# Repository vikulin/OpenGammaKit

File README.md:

# OpenGammaKit

## PCB front and back side

<table>
  <tr>
    <td align="center">
      
      <br><b>Front view</b>
    </td>
    <td align="center">
      
      <br><b>Back view</b>
    </td>
  </tr>
</table>

**OpenGammaKit** is an open-source gamma spectrometer hardware platform, inspired by the excellent [Open-Gamma-Detector](https://github.com/OpenGammaProject/Open-Gamma-Detector). It takes the original schematic and redesigns the PCB using **KiCad** (originally designed in EasyEDA), making the project more accessible and modifiable for open hardware enthusiasts.

OpenGammaKit is designed to be affordable, reliable, and easy to integrate with embedded systems, mobile devices, or PCs—ideal for DIY nuclear instrumentation, educational labs, or citizen science.

---

## Order the PCB or PCB + Assembly

You can order the **Open Gamma Kit** PCB or a fully assembled board from PCBWay or any other PCB manufacturer.
Also Epic Crystal 1inch NaI(Tl) crystal can be used for the prototype:
[NaI(Tl) crystal](https://www.epic-scintillator.com/NaI-scintillator-1inchx1inch)

---

## 🔧 Features

- ✅ Based on the **Open-Gamma-Detector** schematic  
- ✅ Complete redesign in **KiCad** with improved layout and routing  
- ✅ USB serial communication (compatible with Android 7.0+ and PCs)  
- ✅ Compatible with [OGK Inspector](https://github.com/vikulin/OGK-Inspector) Android app and [OGK Firmware](https://github.com/vikulin/OGK-Firmware) 
- ✅ Real-time gamma spectrum output and spectrometer integration  
- ✅ Works with scintillation detectors (e.g., CsI(Tl), NaI(Tl), etc.)  
- ✅ Open and editable source files for schematics and PCB

---

## 📘Assembly guide, 3D models for enclosure

https://github.com/vikulin/OGK-3D-Models

---

## 📂 Repository Contents

- `/docs/` – Spectrum([OGK Inspector](https://github.com/vikulin/OGK-Inspector))
- `/kicad-libraries/` – KiCad libraries, including custom footprints

---

## 📷 3D render previews of the boards

<p align="center">
  <br>
  
  <br>
  
</p>

---

## 📦 Release Contents

OpenGammaKit releases version **0.1.5.5** and later include all the fabrication files required to manufacture and assemble the OpenGammaKit gamma spectrometer hardware:

| File Name                                     | Description                                                                |
| --------------------------------------------- | -------------------------------------------------------------------------- |
| `open-gamma-kit-gerber-files-<version>.zip`   | 🟢 Complete Gerber and Drill files for PCB fabrication.                    |
| `open-gamma-kit-centroid-file-<version>.csv`  | 📍 Centroid (Pick-and-Place) file in mils for automated assembly.          |
| `open-gamma-kit-<version>.pdf`                | 📄 PDF documentation                                                       |
| `BOM.csv`                                     | 📋 Bill of Materials (not archived — listed separately).                   |

📁 **Location**: All files are available in the [Assets](https://github.com/vikulin/OpenGammaKit/releases) release section.

---

## 🧠 Companion Projects

- **OGK Inspector (Android App)**  
  View spectra, calculate resolution, access terminal mode  
  👉 [OGK-Inspector on GitHub](https://github.com/vikulin/OGK-Inspector)

- **OGK Firmware**  
  USB serial interface firmware for supported microcontrollers  
  👉 [OGK Firmware Repository](https://github.com/vikulin/OGK-Firmware)

---

## Spectrum of ²⁴¹Am source measured with NaI(Tl) detector
| Element | Symbol | Atomic Number | Mass Number |
|---------|--------|----------------|--------------|
| Americium | Am     | 95             | 241          |

The spectrum clearly shows two gamma peaks at **59.54 keV** and **26.35 keV**, both corresponding to emissions from ²⁴¹Am:

- The **59.54 keV** peak is the most intense and commonly used for energy calibration.
- The **26.35 keV** peak is weaker but still visible, depending on detector resolution and shielding conditions.

<p align="center">
  <br>
  
</p>

> 📌 These lines are useful for calibration and spectral identification in low-energy gamma spectroscopy using NaI(Tl) detectors.

---

## 📜 License

This project is licensed under the **GNU General Public License v3.0**.  
See the [LICENSE](LICENSE) file for details.

---

## 🙌 Acknowledgements

- Based on the original design by [OpenGammaProject](https://github.com/OpenGammaProject/Open-Gamma-Detector)  
- Thanks to the open hardware and spectroscopy communities!

---

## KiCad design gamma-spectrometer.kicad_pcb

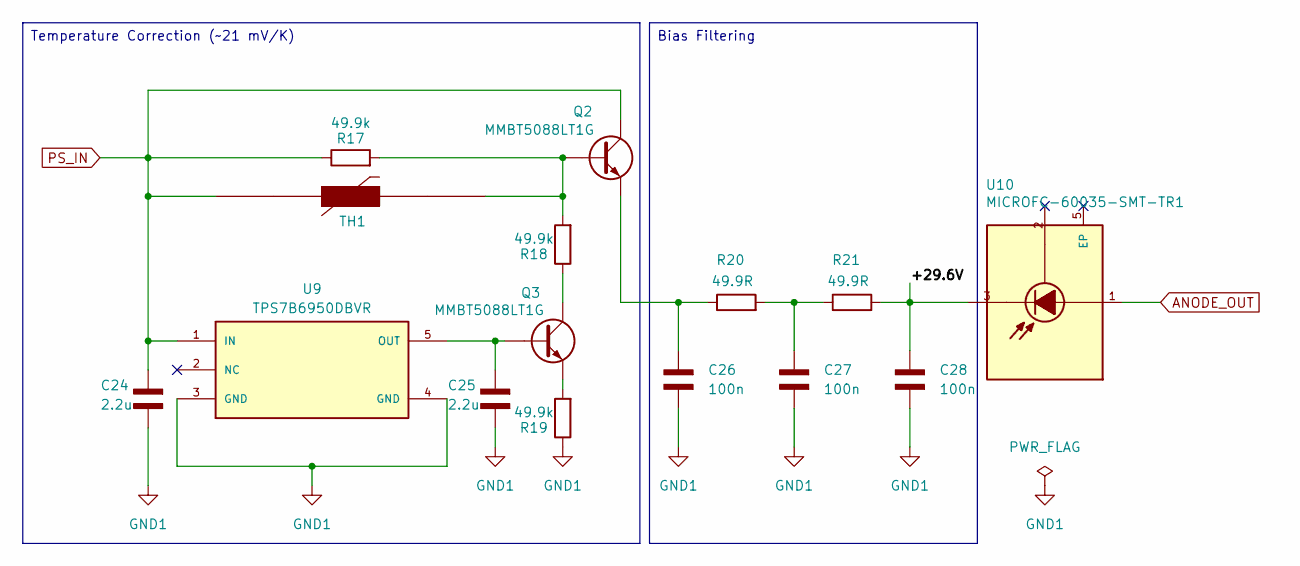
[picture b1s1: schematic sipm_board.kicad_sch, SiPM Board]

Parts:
C24, C25: 2.2u; C_0603_1608Metric
C26, C27, C28: 100n; CAPC1608X90N; PARTREV NA
Q2, Q3: MMBT5088LT1G; SOT95P237X111-3N
R17, R18, R19: 49.9k; RES_ERJ3EKF4992V
R20, R21: 49.9R; RES_ERJ3EKF49R9V
TH1: Thermistor_PTC; NTCS0603E3103FLT
U9: TPS7B6950DBVR; SOT95P280X145-5N
U10: MICROFC-60035-SMT-TR1; XDCR_MICROFC-60035-SMT-TR1; PARTREV 31 JUL 2018

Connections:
/SiPM Board/+29.6V: C28.2, R21.2, U10.3
ANODE_OUT: U10.1
GND1: C24.2, C25.2, C26.1, C27.1, C28.1, R19.1, U9.3 (GND), U9.4 (GND)
unnamed: C27.2, R20.2, R21.1
unnamed: Q2.2 (B), R17.2, R18.2, TH1.1
unnamed: C26.2, Q2.3 (E), R20.1
unnamed: C25.1, Q3.2 (B), U9.5 (OUT)
unnamed: Q3.1 (C), R18.1
unnamed: Q3.3 (E), R19.2
PS_IN: C24.1, Q2.1 (C), R17.1, TH1.2, U9.1 (IN)

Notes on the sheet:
Bias Filtering
Temperature Correction (~21 mV/K)

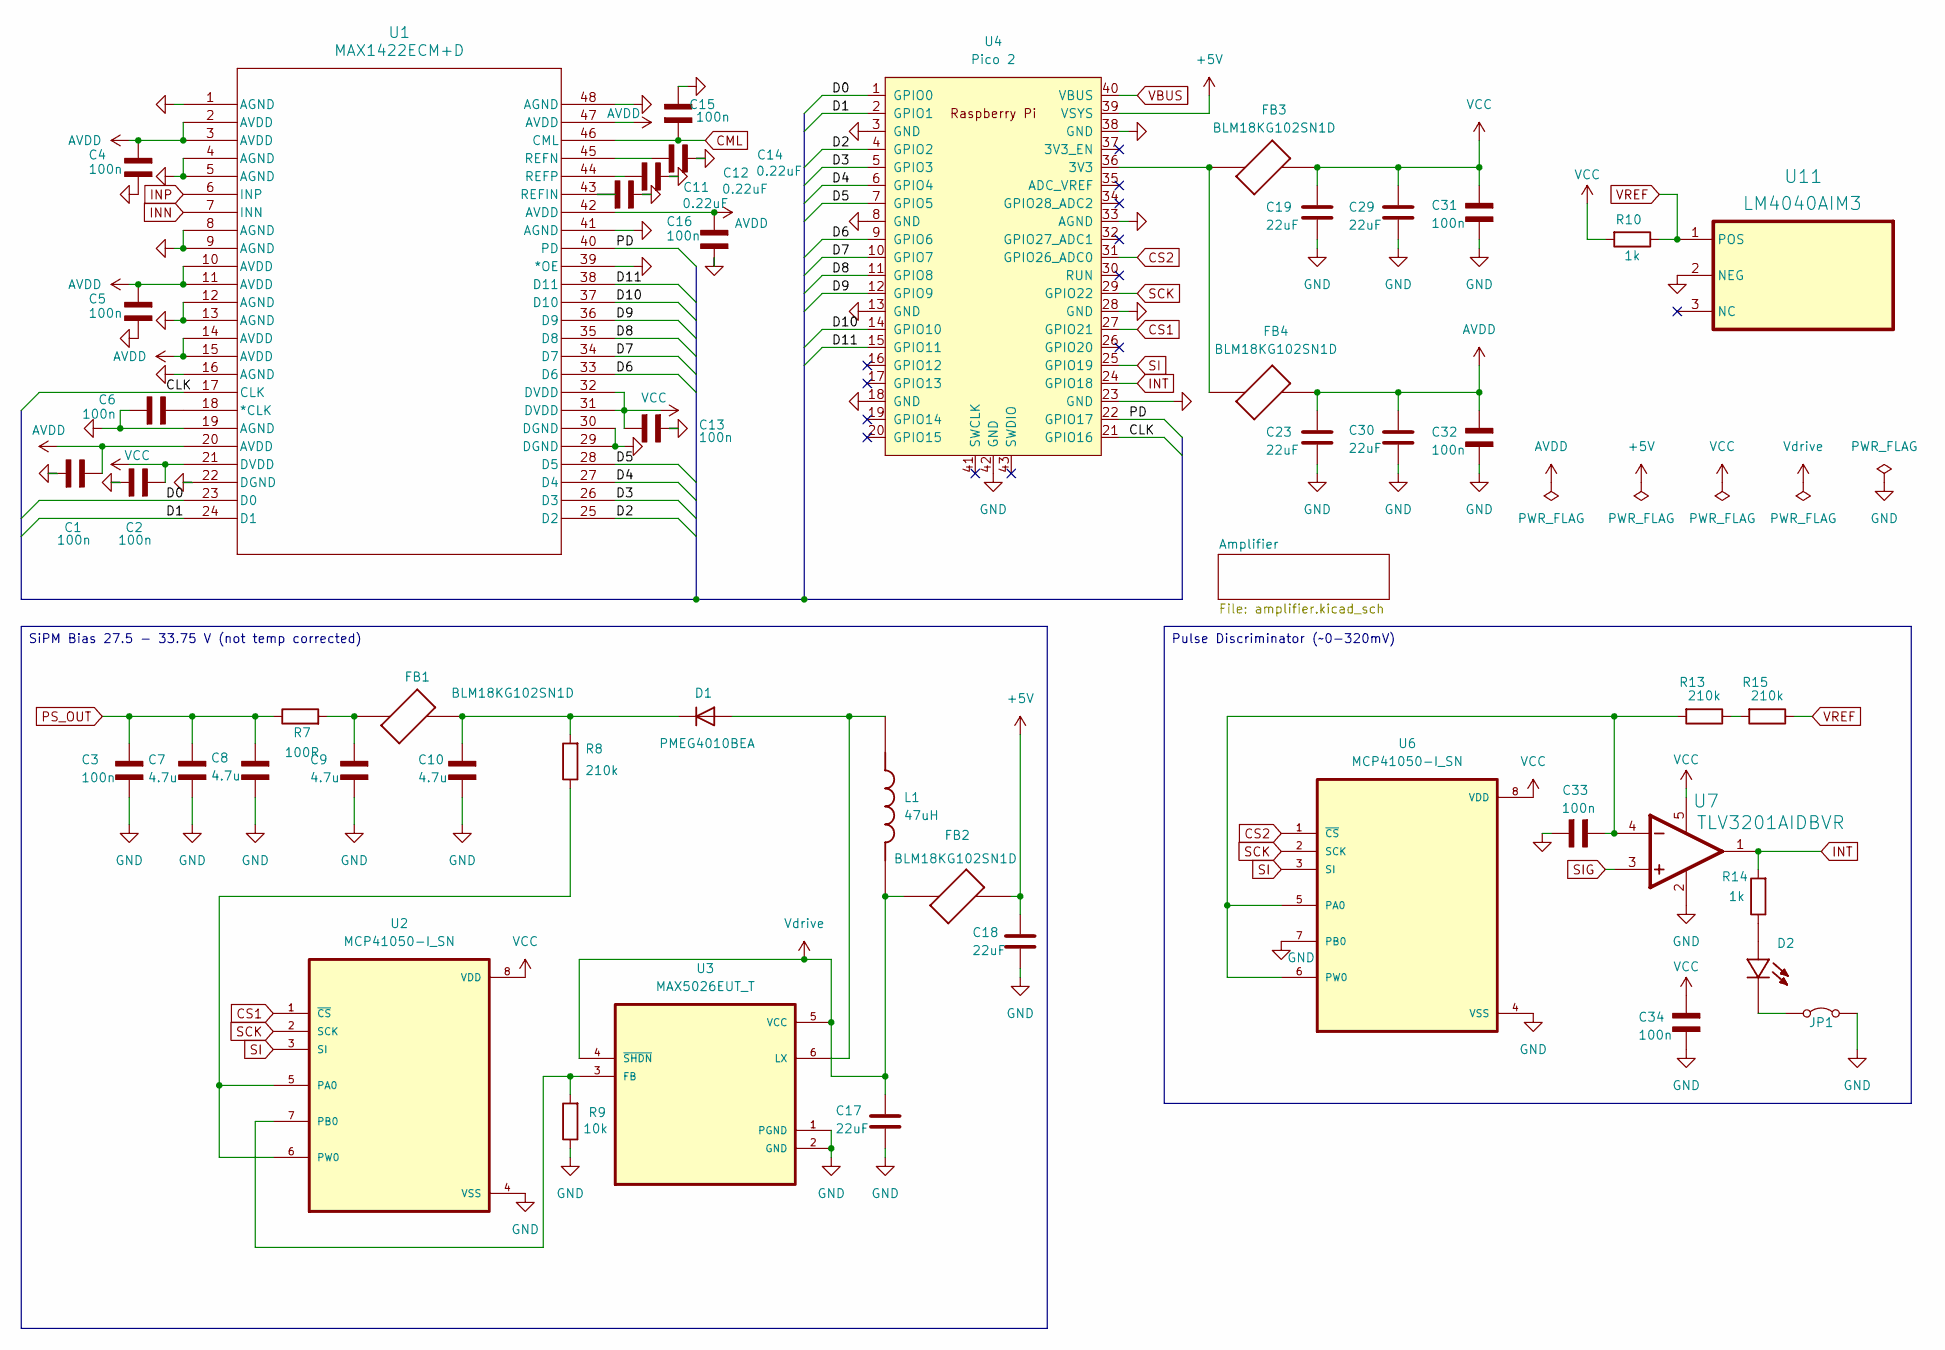
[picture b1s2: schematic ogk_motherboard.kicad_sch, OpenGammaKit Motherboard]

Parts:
C1, C2, C3, C4, C5, C6, C13, C15, C16, C31, C32, C33, C34: 100n; CAPC1608X90N; PARTREV NA
C7, C8, C9, C10: 4.7u; CAPC2012X140N
C11, C12, C14: 0.22uF; CAPC1608X90N
C17, C18, C19, C23, C29, C30: 22uF; CAPC1608X90N
D1: PMEG4010BEA; DIO_BZX384-C30_115
D2: LTST-C190KGKT; LEDC1608X35N
FB1, FB2, FB3, FB4: BLM18KG102SN1D; BEADC1608X95N
JP1: SolderJumper-2_P1.3mm_Open_TrianglePad1.0x1.5mm
L1: 47uH; IND_NRS4018T470MDGJ; PARTREV 2021.10.25
R7: 100R; RES_ERJ3EKF1000V
R8, R13, R15: 210k; RES_ERJ3EKF2103V
R9: 10k; RES_ERJ3EKF1002V
R10, R14: 1k; RES_ERJ3EKF1001V
U1: MAX1422ECM+D; 21-0054G_48_MXM
U2, U6: MCP41050-I_SN; SOIC127P600X175-8N
U3: MAX5026EUT_T; SOT95P280X145-6N
U4: Pico 2; RPi_Pico_SMD_TH
U7: TLV3201AIDBVR; SOT95P280X145-5N
U11: LM4040AIM3; SOT95P237X112-3N

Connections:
+5V: C18.1, FB2.2, U4.39 (VSYS)
/Motherboard/CLK: U1.17 (CLK), U4.21 (GPIO16)
/Motherboard/D0: U1.23 (D0), U4.1 (GPIO0)
/Motherboard/D1: U1.24 (D1), U4.2 (GPIO1)
/Motherboard/D2: U1.25 (D2), U4.4 (GPIO2)
/Motherboard/D3: U1.26 (D3), U4.5 (GPIO3)
/Motherboard/D4: U1.27 (D4), U4.6 (GPIO4)
/Motherboard/D5: U1.28 (D5), U4.7 (GPIO5)
/Motherboard/D6: U1.33 (D6), U4.9 (GPIO6)
/Motherboard/D7: U1.34 (D7), U4.10 (GPIO7)
/Motherboard/D8: U1.35 (D8), U4.11 (GPIO8)
/Motherboard/D9: U1.36 (D9), U4.12 (GPIO9)
/Motherboard/D10: U1.37 (D10), U4.14 (GPIO10)
/Motherboard/D11: U1.38 (D11), U4.15 (GPIO11)
/Motherboard/PD: U1.40 (PD), U4.22 (GPIO17)
AVDD: C1.2, C4.2, C5.2, C16.2, C23.1, C30.1, C32.2, FB4.2, U1.2 (AVDD), U1.3 (AVDD), U1.10 (AVDD), U1.11 (AVDD), U1.14 (AVDD), U1.15 (AVDD), U1.20 (AVDD), U1.42 (AVDD), U1.47 (AVDD)
CML: C15.2, U1.46 (CML); also elsewhere on the board
CS1: U2.1 (~CS), U4.27 (GPIO21)
CS2: U4.31 (GPIO26_ADC0), U6.1 (~CS)
GND: C1.1, C2.1, C3.1, C4.1, C5.1, C6.1, C7.2, C8.2, C9.2, C10.2, C11.2, C12.2, C13.1, C14.2, C15.1, C16.1, C17.2, C18.2, C19.2, C23.2, C29.2, C30.2, C31.1, C32.1, C33.2, C34.1, JP1.2 (B), R9.1, U1.1 (AGND), U1.4 (AGND), U1.5 (AGND), U1.8 (AGND), U1.9 (AGND), U1.12 (AGND), U1.13 (AGND), U1.16 (AGND), U1.19 (AGND), U1.22 (DGND), U1.29 (DGND), U1.30 (DGND), U1.39 (*OE), U1.41 (AGND), U1.48 (AGND), U2.4 (VSS), U3.1 (PGND), U3.2 (GND), U4.3 (GND), U4.8 (GND), U4.13 (GND), U4.18 (GND), U4.23 (GND), U4.28 (GND), U4.33 (AGND), U4.38 (GND), U4.42 (GND), U6.4 (VSS), U6.7 (PB0), U7.2 (GND), U11.2 (NEG); also elsewhere on the board
INN: U1.7 (INN); also elsewhere on the board
INP: U1.6 (INP); also elsewhere on the board
INT: R14.2, U4.24 (GPIO18), U7.1 (OUT)
unnamed: C9.1, FB1.1, R7.2
unnamed: D1.2 (A), L1.1, U3.6 (LX)
unnamed: C10.1, D1.1 (K), FB1.2, R8.2
unnamed: D2.A, R14.1
unnamed: D2.C, JP1.1 (A)
unnamed: R13.1, R15.2
unnamed: C6.2, U1.18 (*CLK)
unnamed: C11.1, U1.43 (REFIN)
unnamed: C14.1, U1.45 (REFN)
unnamed: C12.1, U1.44 (REFP)
unnamed: R8.1, U2.5 (PA0), U2.6 (PW0)
unnamed: R9.2, U2.7 (PB0), U3.3 (FB)
unnamed: FB3.1, FB4.1, U4.36 (3V3)
unnamed: C33.1, R13.2, U6.5 (PA0), U6.6 (PW0), U7.4 (IN-)
PS_OUT: C3.2, C7.1, C8.1, R7.1
SCK: U2.2 (SCK), U4.29 (GPIO22), U6.2 (SCK)
SI: U2.3 (SI), U4.25 (GPIO19), U6.3 (SI)
SIG: U7.3 (IN+); also elsewhere on the board
VBUS: U4.40 (VBUS)
VCC: C2.2, C13.2, C19.1, C29.1, C31.2, C34.2, FB3.2, R10.2, U1.21 (DVDD), U1.31 (DVDD), U1.32 (DVDD), U2.8 (VDD), U6.8 (VDD), U7.5 (VCC); also elsewhere on the board
VREF: R10.1, R15.1, U11.1 (POS)
Vdrive: C17.1, FB2.1, L1.2, U3.4 (~SHDN), U3.5 (VCC)

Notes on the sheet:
Pulse Discriminator (~0-320mV)
SiPM Bias 27.5 - 33.75 V (not temp corrected)

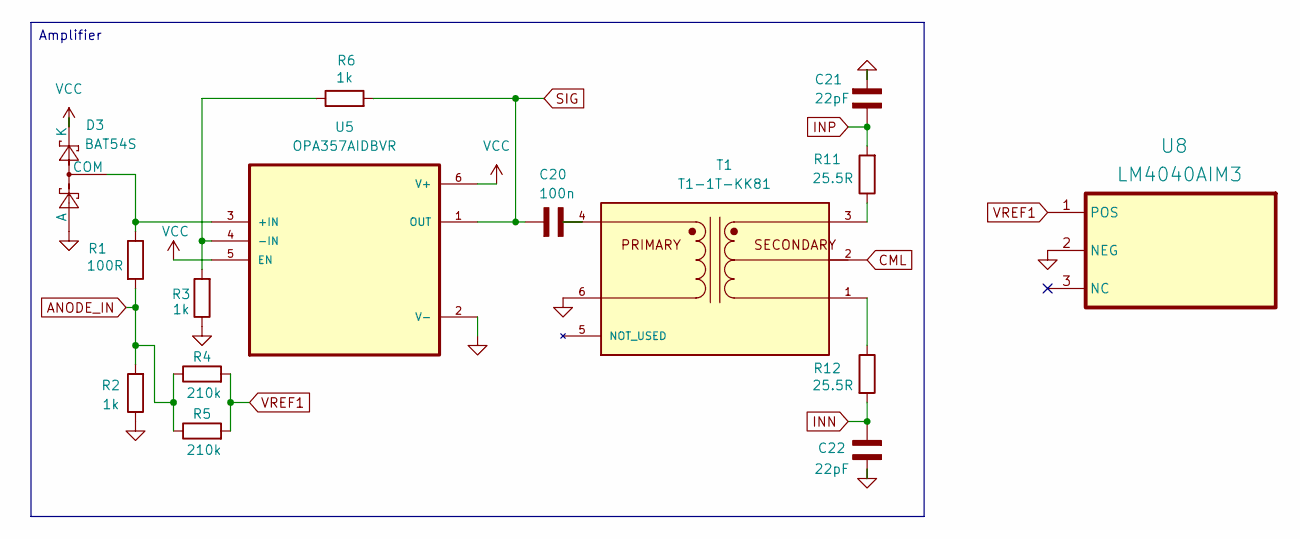
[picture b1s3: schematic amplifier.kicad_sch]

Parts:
C20: 100n; CAPC1608X90N; PARTREV NA
C21, C22: 22pF; CAPC1608X90N; PARTREV 11-Oct-17
D3: BAT54S; SOT-23
R1: 100R; RES_ERJ3EKF1000V
R2, R3, R6: 1k; RES_ERJ3EKF1001V
R4, R5: 210k; RES_ERJ3EKF2103V; PARTREV 3/1/2020
R11, R12: 25.5R; RES_ERJ3EKF25R5V
T1: T1-1T-KK81; XFMR_T1-1T-KK81_; PARTREV B
U5: OPA357AIDBVR; SOT95P280X145-6N
U8: LM4040AIM3; SOT95P237X112-3N

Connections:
ANODE_IN: R1.2, R2.2, R4.1, R5.1
CML: T1.2; also elsewhere on the board
GND: C21.1, C22.1, D3.1 (A), R2.1, R3.1, T1.6, U5.2 (V-), U8.2 (NEG); also elsewhere on the board
INN: C22.2, R12.2; also elsewhere on the board
INP: C21.2, R11.2; also elsewhere on the board
unnamed: C20.2, T1.4
unnamed: D3.3 (COM), R1.1, U5.3 (+IN)
unnamed: R11.1, T1.3
unnamed: R12.1, T1.1
unnamed: R3.2, R6.1, U5.4 (-IN)
SIG: C20.1, R6.2, U5.1 (OUT); also elsewhere on the board
VCC: D3.2 (K), U5.5 (EN), U5.6 (V+); also elsewhere on the board
VREF1: R4.2, R5.2, U8.1 (POS)

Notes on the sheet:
Amplifier

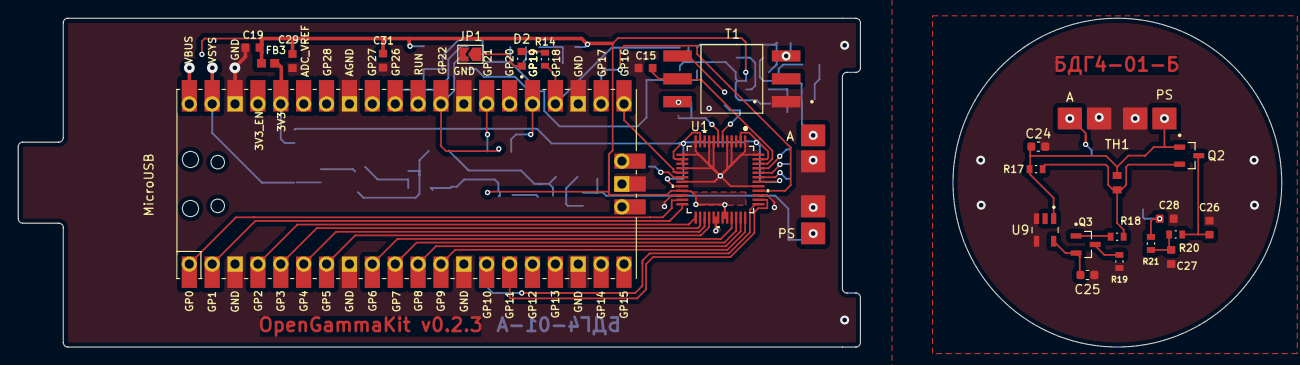
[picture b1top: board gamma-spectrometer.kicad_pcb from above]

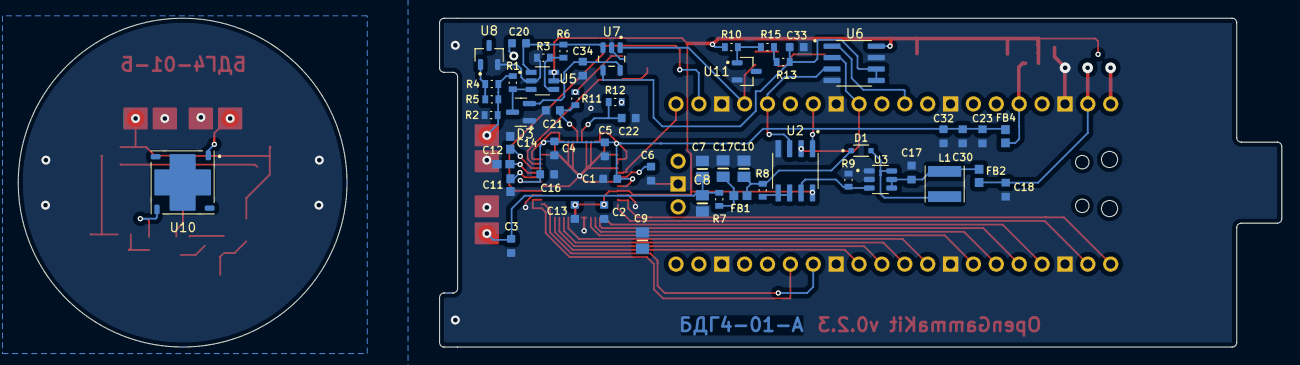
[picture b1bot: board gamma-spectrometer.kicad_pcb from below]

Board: 2 copper layers, 140.3 x 36.5 mm, 79 parts (54 on the bottom side), 60 nets.

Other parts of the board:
C17#2: 4.7u; CAPC2012X140N

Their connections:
GND: C17#2.2; also elsewhere on the board

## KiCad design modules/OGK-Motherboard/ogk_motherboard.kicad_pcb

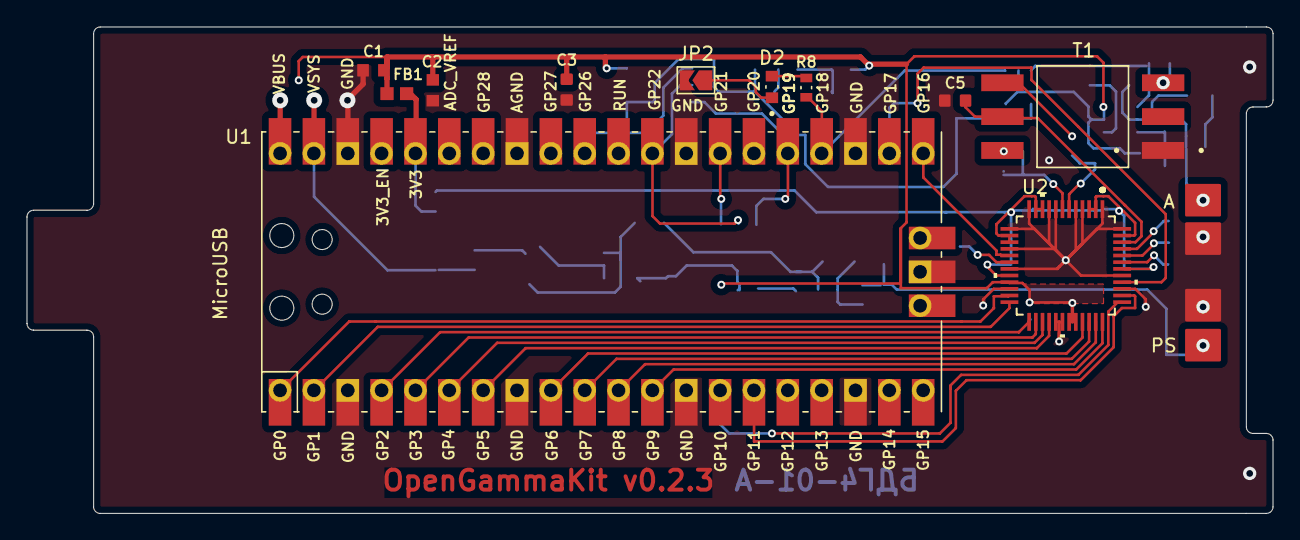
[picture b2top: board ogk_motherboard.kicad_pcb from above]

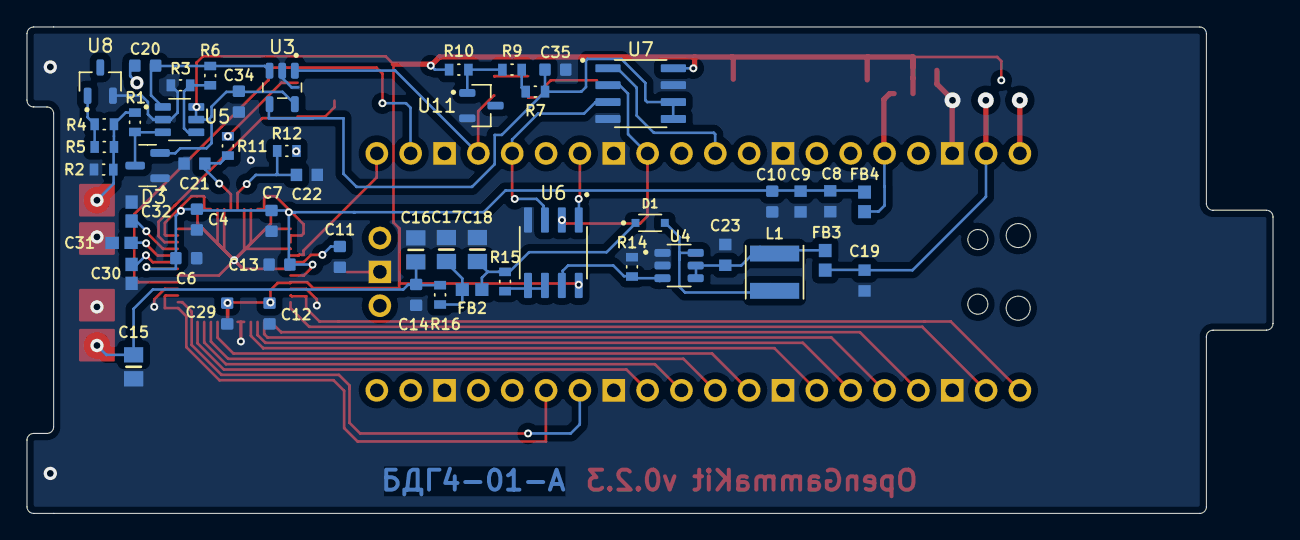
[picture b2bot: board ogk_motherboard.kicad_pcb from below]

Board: 2 copper layers, 93.5 x 36.5 mm, 63 parts (52 on the bottom side), 51 nets.

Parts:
C1, C2, C8, C9, C19, C23: 22uF; CAPC1608X90N
C3, C4, C5, C6, C7, C10, C11, C12, C13, C14, C20, C29, C34, C35: 100n; CAPC1608X90N
C15, C16, C17, C18: 4.7u; CAPC2012X140N
C21, C22: 22pF; CAPC1608X90N
C30, C31, C32: 0.22uF; CAPC1608X90N
D1: PMEG4010BEA; DIO_BZX384-C30_115
D2: LTST-C190KGKT; LEDC1608X35N
D3: BAT54S; SOT-23
FB1, FB2, FB3, FB4: BLM18KG102SN1D; BEADC1608X95N
JP2: SolderJumper-2_P1.3mm_Open_TrianglePad1.0x1.5mm
L1: 47uH; IND_NRS4018T470MDGJ
R1, R16: 100R; RES_ERJ3EKF1000V
R2, R3, R6, R8, R10: 1k; RES_ERJ3EKF1001V
R4, R5, R7, R9, R15: 210k; RES_ERJ3EKF2103V
R11, R12: 25.5R; RES_ERJ3EKF25R5V
R14: 10k; RES_ERJ3EKF1002V
T1: T1-1T-KK81; XFMR_T1-1T-KK81_
U1: Pico 2; RPi_Pico_SMD_TH
U2: MAX1422ECM+D; 21-0054G_48_MXM
U3: TLV3201AIDBVR; SOT95P280X145-5N
U4: MAX5026EUT_T; SOT95P280X145-6N
U5: OPA357AIDBVR; SOT95P280X145-6N
U6, U7: MCP41050-I_SN; SOIC127P600X175-8N
U8, U11: LM4040AIM3; SOT95P237X112-3N

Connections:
+5V: C19.1, FB3.2, U1.39 (VSYS)
/CLK: U1.21 (GPIO16), U2.17 (CLK)
/D0: U1.1 (GPIO0), U2.23 (D0)
/D1: U1.2 (GPIO1), U2.24 (D1)
/D2: U1.4 (GPIO2), U2.25 (D2)
/D3: U1.5 (GPIO3), U2.26 (D3)
/D4: U1.6 (GPIO4), U2.27 (D4)
/D5: U1.7 (GPIO5), U2.28 (D5)
/D6: U1.9 (GPIO6), U2.33 (D6)
/D7: U1.10 (GPIO7), U2.34 (D7)
/D8: U1.11 (GPIO8), U2.35 (D8)
/D9: U1.12 (GPIO9), U2.36 (D9)
/D10: U1.14 (GPIO10), U2.37 (D10)
/D11: U1.15 (GPIO11), U2.38 (D11)
/PD: U1.22 (GPIO17), U2.40 (PD)
ANODE_IN: R1.2, R2.2, R4.1, R5.1
AVDD: C4.2, C6.2, C7.2, C8.1, C9.1, C10.2, C13.2, FB4.2, U2.2 (AVDD), U2.3 (AVDD), U2.10 (AVDD), U2.11 (AVDD), U2.14 (AVDD), U2.15 (AVDD), U2.20 (AVDD), U2.42 (AVDD), U2.47 (AVDD)
CML: C5.2, T1.2, U2.46 (CML)
CS1: U1.27 (GPIO21), U6.1 (~CS)
CS2: U1.31 (GPIO26_ADC0), U7.1 (~CS)
GND: C1.2, C2.2, C3.1, C4.1, C5.1, C6.1, C7.1, C8.2, C9.2, C10.1, C11.1, C12.1, C13.1, C14.1, C15.2, C16.2, C17.2, C18.2, C19.2, C21.1, C22.1, C23.2, C29.1, C30.2, C31.2, C32.2, C34.1, C35.2, D3.1 (A), JP2.2 (B), R2.1, R3.1, R14.1, T1.6, U1.3 (GND), U1.8 (GND), U1.13 (GND), U1.18 (GND), U1.23 (GND), U1.28 (GND), U1.33 (AGND), U1.38 (GND), U1.42 (GND), U2.1 (AGND), U2.4 (AGND), U2.5 (AGND), U2.8 (AGND), U2.9 (AGND), U2.12 (AGND), U2.13 (AGND), U2.16 (AGND), U2.19 (AGND), U2.22 (DGND), U2.29 (DGND), U2.30 (DGND), U2.39 (*OE), U2.41 (AGND), U2.48 (AGND), U3.2 (GND), U4.1 (PGND), U4.2 (GND), U5.2 (V-), U6.4 (VSS), U7.4 (VSS), U7.7 (PB0), U8.2 (NEG), U11.2 (NEG)
INN: C22.2, R12.2, U2.7 (INN)
INP: C21.2, R11.2, U2.6 (INP)
INT: R8.2, U1.24 (GPIO18), U3.1 (OUT)
unnamed: C17.1, FB2.1, R16.2
unnamed: C20.2, T1.4
unnamed: D1.2 (A), L1.1, U4.6 (LX)
unnamed: C18.1, D1.1 (K), FB2.2, R15.2
unnamed: D2.A, R8.1
unnamed: D3.3 (COM), R1.1, U5.3 (+IN)
unnamed: D2.C, JP2.1 (A)
unnamed: R7.1, R9.2
unnamed: R11.1, T1.3
unnamed: R12.1, T1.1
unnamed: FB1.1, FB4.1, U1.36 (3V3)
unnamed: C11.2, U2.18 (*CLK)
unnamed: C30.1, U2.43 (REFIN)
unnamed: C32.1, U2.45 (REFN)
unnamed: C31.1, U2.44 (REFP)
unnamed: C35.1, R7.2, U3.4 (IN-), U7.5 (PA0), U7.6 (PW0)
unnamed: R14.2, U4.3 (FB), U6.7 (PB0)
unnamed: R3.2, R6.1, U5.4 (-IN)
unnamed: R15.1, U6.5 (PA0), U6.6 (PW0)
PS_OUT: C14.2, C15.1, C16.1, R16.1
SCK: U1.29 (GPIO22), U6.2 (SCK), U7.2 (SCK)
SI: U1.25 (GPIO19), U6.3 (SI), U7.3 (SI)
SIG: C20.1, R6.2, U3.3 (IN+), U5.1 (OUT)
VCC: C1.1, C2.1, C3.2, C12.2, C29.2, C34.2, D3.2 (K), FB1.2, R10.2, U2.21 (DVDD), U2.31 (DVDD), U2.32 (DVDD), U3.5 (VCC), U5.5 (EN), U5.6 (V+), U6.8 (VDD), U7.8 (VDD)
VREF: R9.1, R10.1, U11.1 (POS)
VREF1: R4.2, R5.2, U8.1 (POS)
Vdrive: C23.1, FB3.1, L1.2, U4.4 (~SHDN), U4.5 (VCC)

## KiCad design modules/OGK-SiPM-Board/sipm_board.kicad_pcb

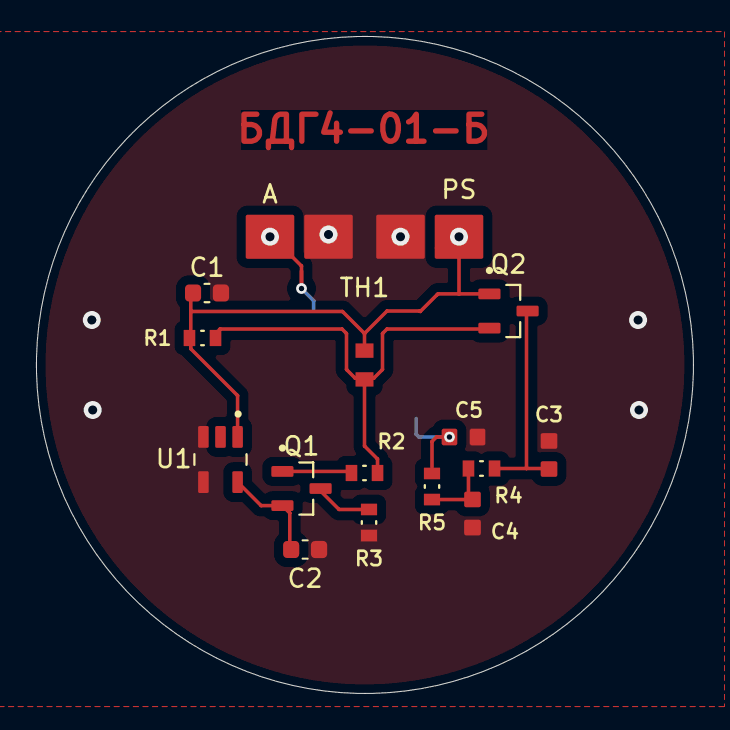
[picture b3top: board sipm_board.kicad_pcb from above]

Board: 2 copper layers, 36.5 x 36.5 mm, 15 parts (1 on the bottom side), 9 nets.

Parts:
C1, C2: 2.2u; C_0603_1608Metric
C3, C4, C5: 100n; CAPC1608X90N
Q1, Q2: MMBT5088LT1G; SOT95P237X111-3N
R1, R2, R3: 49.9k; RES_ERJ3EKF4992V
R4, R5: 49.9R; RES_ERJ3EKF49R9V
TH1: Thermistor_PTC; NTCS0603E3103FLT
U1: TPS7B6950DBVR; SOT95P280X145-5N
U2: MICROFC-60035-SMT-TR1; XDCR_MICROFC-60035-SMT-TR1

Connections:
/+29.6V: C5.2, R5.2, U2.3
GND1: C1.2, C2.2, C3.1, C4.1, C5.1, R3.1, U1.3 (GND), U1.4 (GND)
unnamed: C4.2, R4.2, R5.1
unnamed: C2.1, Q1.2 (B), U1.5 (OUT)
unnamed: Q1.1 (C), R2.1
unnamed: Q1.3 (E), R3.2
unnamed: Q2.2 (B), R1.2, R2.2, TH1.1
unnamed: C3.2, Q2.3 (E), R4.1
PS_IN: C1.1, Q2.1 (C), R1.1, TH1.2, U1.1 (IN)

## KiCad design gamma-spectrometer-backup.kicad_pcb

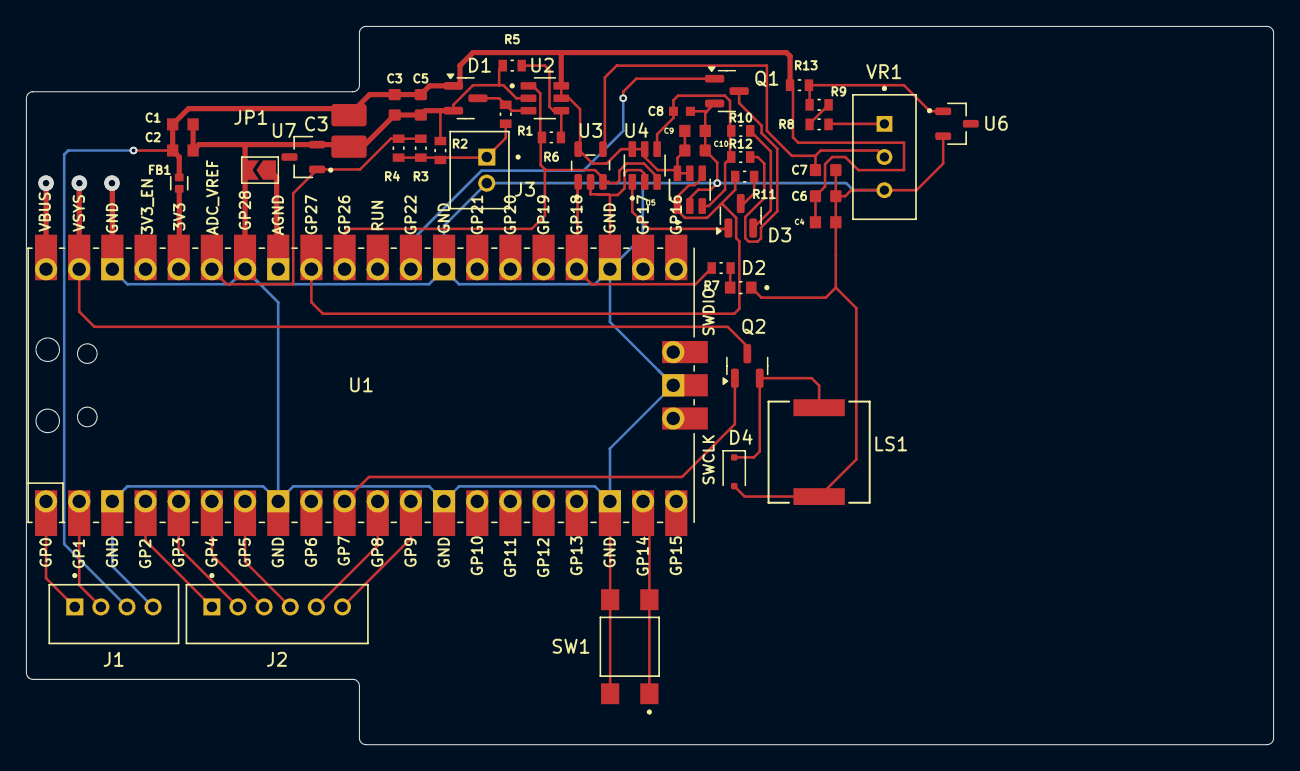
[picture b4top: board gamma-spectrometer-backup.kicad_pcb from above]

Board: 2 copper layers, 95.5 x 55.0 mm, 45 parts (0 on the bottom side), 34 nets.

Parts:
C1, C2, C4, C9: 22uF; CAPC1608X90N
C3, C5, C6, C7, C10: 100n; CAPC1608X90N
C3#2: 100nF; VARC3224X170N
C8: 470p; CAP_ECHU1C471JX5
D1, D3: BAT54S; SOT-23
D2: LTST-C190KGKT; LEDC1608X35N
D4: PMEG4010BEA,115; D_SOD-323F
FB1: ACML-0402HC-301-T; BEADC1005X65N
J1: *; JST_B4B-PH-K-S(LF)(SN)
J2: *; JST_B6B-PH-K-S(LF)(SN)
J3: *; JST_B2B-PH-K-S(LF)(SN)
JP1: SolderJumper-2_P1.3mm_Open_TrianglePad1.0x1.5mm
LS1: AST0760MCTRQ (6kHz); AST0760_MAL
Q1, Q2: 2N7002; SOT-23
R1, R10: 100R; RES_ERJ3EKF2103V
R2, R5, R7, R12, R13: 1k; RES_ERJ3EKF2103V
R3, R4, R8, R9: 210k; RES_ERJ3EKF2103V
R6: 2.1k; RES_ERJ3EKF2103V
R11: 10k; RES_ERJ3EKF2103V
SW1: *; SW_TL3305AF160QG
U1: Pico 2; RPi_Pico_SMD_TH
U2, U4, U5: OPA357AIDBVR; SOT95P280X145-6N
U3: TLV3201AIDBVR; SOT95P280X145-5N
U6, U7: LM4040AIM3-3.0+T; SOT95P237X112-3N
VR1: 50k; TRIM_3296W-1-503LF

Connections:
+5V: Q2.3 (D), U1.39 (VSYS)
ANODE: J3.1, R1.1, R2.2, R3.1, R4.1
CS: J2.4, U1.7 (GPIO5)
GND: C1.2, C2.2, C3.1, C3#2.2, C4.2, C5.1, C6.1, C7.2, C8.1, C9.2, C10.1, D1.2 (K), D2.C, D4.2 (A), J1.4, J3.2, JP1.2 (B), LS1.2, Q1.2 (S), R2.1, R5.1, SW1.3, SW1.4, U1.3 (GND), U1.8 (GND), U1.13 (GND), U1.18 (GND), U1.23 (GND), U1.28 (GND), U1.34 (GPIO28_ADC2), U1.38 (GND), U1.42 (GND), U2.2 (V-), U3.2 (GND), U4.2 (V-), U5.2 (V-), U6.2 (NEG), U7.2 (NEG), VR1.3 (CW)
INT: R7.2, U1.24 (GPIO18), U3.1 (OUT)
unnamed: D1.3 (COM), R1.2, U2.3 (+IN)
unnamed: D2.A, R7.1
unnamed: D3.1 (A), U4.1 (OUT)
unnamed: D3.3 (COM), R11.1
unnamed: D3.2 (K), R10.1
unnamed: D4.1 (K), LS1.1, Q2.2 (S)
unnamed: JP1.1 (A), U1.33 (AGND)
unnamed: Q1.3 (D), R12.2
unnamed: R8.2, R9.2
unnamed: FB1.1, U1.36 (3V3)
unnamed: SW1.1, SW1.2, U1.19 (GPIO14)
unnamed: R5.2, R6.1, U2.4 (-IN)
unnamed: C7.1, U3.4 (IN-), VR1.2 (WIPER)
unnamed: C8.2, R10.2, R12.1, U4.4 (-IN), U5.3 (+IN)
unnamed: R8.1, VR1.1 (CCW)
PEAK: R11.2, U1.32 (GPIO27_ADC1), U5.1 (OUT), U5.4 (-IN)
RST: Q1.1 (G), U1.29 (GPIO22)
RX: J2.3, U1.6 (GPIO4)
SCK: J2.1, U1.4 (GPIO2)
SCL: J1.2, U1.2 (GPIO1)
SDA: J1.1, U1.1 (GPIO0)
SIG: R6.2, U1.31 (GPIO26_ADC0), U2.1 (OUT), U3.3 (IN+), U4.3 (+IN)
TCKR: Q2.1 (G), U1.10 (GPIO7)
TX: J2.2, U1.5 (GPIO3)
UART1RX: J2.6, U1.12 (GPIO9)
UART1TX: J2.5, U1.11 (GPIO8)
VCC: C1.1, C2.1, C3.2, C3#2.1, C4.1, C5.2, C6.2, C9.1, C10.2, D1.1 (A), FB1.2, J1.3, R13.2, U2.5 (EN), U2.6 (V+), U3.5 (VCC), U4.5 (EN), U4.6 (V+), U5.5 (EN), U5.6 (V+)
VREF: R3.2, R4.2, U1.35 (ADC_VREF), U7.1 (POS)
VREF1: R9.1, R13.1, U6.1 (POS)

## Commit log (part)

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2025-01-23 Description update
2025-01-23 Removed obsolete file
2025-01-23 Create LICENSE
2025-01-23 Exclude autosave files
2025-01-23 Removed cache
2025-01-23 Added drl files
2025-01-23 Corrected labels
2025-01-24 Added schematic
2025-01-25 Exclude backup files
2025-01-26 U8 5-6 pins connection error fix
2025-01-26 Schematic update
2025-01-26 D1 1-2 pins conenction error fix
2025-01-26 U2 GNS connection error fix
2025-02-09 PCB size fix
2025-02-09 Centered U1
2025-02-09 PCB view update
2025-02-09 Minor fixes
2025-02-09 PCB size fix
    PCB size fix
    Zoomer position adjustment
    Minor fixes
    Centered U1
    PCB view update
2025-02-12 Added BOM
2025-02-19 C3 duplication fix
2025-02-26 Changed schematic for default I2C pins
2025-03-07 Added gain regulator. MHF3 connector for signal line.
2025-04-02 BDG4-01 module boards design
2025-04-03 PCB changes for more precise assembling
2025-04-25 Important fix for SiPM power supply circuit. Moved gerber files.
2025-04-26 Updated BOM, schematic , foortprints, symbols
2025-04-26 Minor changes
2025-05-01 Updated screenshot
2025-05-01 Removed VR2 resistor and adjusted R6 to prevent self-oscillation of the amplifier
2025-05-01 Updated BOM
2025-05-02 Added release publishing workflow
2025-05-03 Update packages for smaller size for VR1,VR2
2025-05-05 Updated BOM format accordingly to PCBWay format
2025-05-06 Centroid files for PCBWay fabrication
2025-05-06 Automatic generation fabrication output files such as Gerber, Drill and Centroid
2025-05-06 Automatic generation fabrication output files such as Gerber, Drill and Centroid. Updated README.
2025-05-06 Corrected manufacturer part#
2025-05-06 Automated Gerber, BOM and Docs generation for release
2025-05-06 Corrected BOM, Automated Gerber and Docs generation for release, bump version
    BOM generation is remaining manual
    Corrected manufacturer part#
    Update build.yml
2025-05-06 Migrated to KiCad 9.0
2025-05-08 Centroid files generation
2025-05-08 PCBWay BOM generation preset
2025-05-08 Added DRC and ERC checks
2025-05-08 ERC errors fix
2025-05-08 Excluded from BOM
2025-05-08 ERC test
2025-05-08 Power flags fix
2025-05-08 Minor change in schematic
2025-05-18 kicad-action version upgrade
2025-05-18 Generated PCB image view
2025-05-18 PCB preview image simensions adjustemnt
2025-05-18 PCB preview image dimensions adjustment
2025-05-21 C17,C19,FB1,FB2,FB3 footprint fix
2025-06-02 Am-241 spectrum update
2025-06-04 Switched to MAX1422 external ADC
2025-06-05 Updated 3d models
2025-06-06 MCP41050 replaces pot for SiPM PS regulation
2025-06-07 ADC capacitors
2025-06-11 Package update
2025-09-07 Digital potentiometer improvement
2025-09-07 Added prerelease condition
2025-09-07 3d models update
2025-09-07 Title fix
2025-09-10 Modular SiPM board
2025-09-10 Removed SiPM code
2025-09-12 Modular motherboard
2026-02-04 Add assembly guide and 3D models link
    Added assembly guide and 3D models section to README.
